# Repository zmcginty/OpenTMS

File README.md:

# Open-Source Transcranial Magnetic Stimulator

An open-source transcranial magnetic stimulator (TMS) project, including coil designs, pulse-generator hardware, and control/charging circuitry.

> **Safety Notice**
> This is **not** a legitimate medical device and is not a substitute for real TMS treatment. This is an experiment I built in my garage, and I cannot verify that it does what it's supposed to (if anyone wants to build an open-source MRI.... let me know...) This device is dangerous, it operates at energy levels more than enough to stop your heart, kill you, blow up and do lots of damage. If you're going to play with high energy pulsed power systems; be careful.

## Table of Contents
- [TMS Coils](#tms-coils)
- [Coil Cooling](#coil-cooling)
- [Coil Materials](#coil-materials)
- [IGBT Switches](#igbt-switches)
- [Gate Drivers](#gate-drivers)
- [Measurement System](#measurement-system)
- [Charging Circuit](#charging-circuit)
- [Pulse-Generator Designs](#pulse-generator-designs)
- [Charge-Control Circuit](#charge-control-circuit)
- [Useful Resources](#useful-resources)
- [TODO](#todo)

---

## TMS Coils

I primarily build two coil geometries — single coils and figure-8 coils. What I've focused on are air-core windings in either single-layer or multi-layer form. The general architecture is adapted from research papers and the limited information published by commercial TMS coil manufacturers. The figure-8 CloudTMS coil (below) was a major influence on my designs in terms of hollow copper conductor carrying coolant.

As I moved to higher pulse rates and energies, active cooling became necessary. My preferred approach, similar to the CloudTMS design, uses hollow copper tubing (sold for HVAC/refrigeration) insulated with PTFE heat-shrink. PTFE works well because it's a good dielectric, stays thin-walled after shrinking, tolerates high temperatures, and holds the coil shape better than thicker heat-shrink alternatives — though it does require fairly high heat to shrink fully.

**Build process:**
- Source 4mm OD / 3mm ID copper tube (5m sections) and 4.5mm, 4:1 PTFE heat-shrink in bulk.
- Feeding heat-shrink onto a long tube run takes patience — compressed air, used to create an air cushion between tube and shrink-wrap, makes this much easier.
- Wind the coil on a custom jig, either single-layer or multi-layer (multi-layer here just means winding randomly around a bobbin rather than stacking discrete single-layer coils).
- Insert something into the copper tube close to the tube's ID (weed-wacker cable works well) during the first few windings to prevent the tube from collapsing, then remove it once winding is complete.
- Hold the coil together with tape ahead of potting.

<p align="center"><em>Example coil before potting</em></p>

Potting the coil in epoxy significantly improves mechanical stability and reduces noise by keeping the windings from moving against each other under pulse forces. Hot glue works as an alternative but produces coils that are noticeably louder in operation — not confidence-inspiring at higher power levels.

<p align="center"><em>Example coil after potting</em></p>

## Coil Cooling

Coils built from hollow copper tube are cooled by pumping coolant through the winding itself.

- **Mineral oil:** Used for a long time — thinner than typical oils but thicker than water. Maintaining ~40°C required roughly 150–200 psi to push enough flow through the coil's small ID. At higher energy levels, I added a water chiller and heat exchanger to pre-cool the oil.
- **Distilled water:** More recently, I've switched to distilled water paired with a diaphragm pump, since the diaphragm provides a degree of electrical isolation between the pump mechanism and the fluid. This is simpler and more effective overall, though there is still a risk of the coolant loop reaching high voltage.

## Coil Materials

| Material | Purpose | Notes |
|---|---|---|
| [Hollow copper tube](https://www.amazon.com/dp/B082FDVNC5) | Water-cooled coil winding | Standard refrigeration-grade tube; cheap and widely available |
| [Fiberglass resin sheet](https://www.amazon.com/dp/B0DYT28W8W) | Application-side coil face | Sturdy, good electrical insulator, and appears permeable to magnetic fields — a disassembled commercial coil used what looked like FR4 fiberglass (PCB-grade) |
| [MAX EPC epoxy potting compound](https://www.amazon.com/dp/B07PMTMKZQ) | Coil potting | Inexpensive, good electrical insulator, decent thermal conductivity. For tube-cooled coils, MAX MCR (lower thermal conductivity) is also an option |

---

## IGBT Switches

My current switch of choice is the **Infineon/Eupec FZ1200R33KF2** — inexpensive and capable of handling substantial power. Prices on eBay range from ~$100–$400, and I've pushed 8kA pulses through a single unit. Adequate snubber capacitance/circuitry is essential to keep the voltage across the device under its 3.3kV rating (I target a safety margin below that).

## Gate Drivers

I've used two Power Integrations gate drivers with this IGBT listed below: but due to limitations and cost, I'm working on designing a custom gate-driver PCB which is still in progress.

- **2SC0535T2G0-33** — Functional, but lacks features like active clamping to protect against turn-off voltage spikes. Requires a custom PCB with gate turn-on/turn-off resistors and capacitors.
- **1SD418F2-FZ1200R33KF2** — Purpose-built for the FZ1200R33KF2; bolts directly onto the device pads. Requires only a 15VDC supply (I use a 1A source). It communicates over two fiber-optic channels (input signal and output/status), which I drive with custom PCBs using AFBR-1624Z HFBR transmitter/receiver modules, controlled by a Teensy 4.1 through a 3.3V→5V level shifter. NOTE: Put fiber-optic receivers (receiving fiber feedback from gate-driver) as close to Teensy/MCU as possible to reduce noise and false fault detection.
- **Custom Gate-Driver (Coming Soon)** — I've noticed that the 1SD418F2 gate drivers I'm using will sometimes detect short-circuits during operation at higher power. This could be legitamite but I'm not exceeding any voltage or current limits as measured by probes. I'm designing a custom gate-driver board since buying gate-drivers new for this IGBT with active-clamping and feedback are over $400, I want to see if I can build them for at most half of that. This will most likely involve having to wind custom isolation-transformers, since I've only found one company who makes isolation transformers rated for ~4-6kV constantly. I've ordered some parts and a 10kV HiPot tester..... more to come later.

---

## Measurement System

### Differential Voltage Measurement
Monitoring Vce (collector-emitter voltage) across each IGBT is critical to staying within its rating — I keep a safety margin and stay below 2.5kV on 3.3kV-rated devices. Since these switches operate on the high side, measurement requires a high-voltage differential probe: I use a **Micsig DP20003** (5600V, 100MHz). A similar, lower-range HV differential probe (1300V) monitors the main capacitor bank voltage.
### Custom HV Diff probe
I'm working on designing a custom HV diff probe since Micsig's new 7kV probe (only other voltage ratings are 700, 1300, 3000) is ~$700, I think it's worth it to try designing a custom probe PCB with isolated dc-dc, voltage divider, and diff opamps. For measuring IGBT voltages, I don't think I need 100MHz bandwidth, so I'm shooting for 50MHz, and hoping to get the price down to less than $100. I'm waiting on boards to show up and will update once I test them! They will probably need to be potted or atleast conformally coated to work in a variety of environments/humidity.

### Current Measurement
A shunt resistor was my first attempt but never produced a trustworthy signal. Two methods have worked well since:

1. **Rogowski coil** — Excellent for high current measurement (AC or DC, no iron core to saturate), but calibrated probes are hard to find secondhand, and a calibrated integrator circuit is needed to get a usable scope signal. I use a calibrated coil from [PowertekUK](https://powertekuk.com) — specifically the [CWTMini](https://powertekuk.com/cwtmini).
2. **Current transformer (CT)** — I use a Tektronix A621 AC current probe (rated to 2kA, available on eBay for $100–$500). In practice, it agrees with the Powertek Rogowski coil up to roughly 8kA despite the rated limit.

---

## Charging Circuit

The charging circuit is a simple, open-loop design: mains power feeds a variable transformer (variac), which drives a microwave oven transformer (MOT) to step up voltage. The stepped-up AC is rectified by a full-bridge rectifier and used to charge the main discharge capacitor bank, which is then discharged through the coil via a high-side switch (latching SCR or non-latching IGBT).

### Microwave Oven Transformers
The current two-switch flyback pulse generator uses two matched MOTs (matched by checking voltage and phase agreement between units — *measurements/resources TODO*). Drawing ~15A at 120V, two matched transformers stay below ~60°C with air cooling alone.

Earlier designs used a single MOT with low-pressure mineral-oil cooling, which worked up to ~14A — but oil cooling systems and pumps added complexity and were prone to leaks.

---

## Pulse-Generator Designs

### Design #1 — SCR-Based Pulse Generator

<p align="center"><em>SCR-switch pulse generator (SCRs are bottom-right. Main capacitor front left. Rectifier behind capacitor. and mineral-oil cooled microwave transformer behid rectifier. </em></p>

The first design I built. It handles very high energy levels well at consistent frequencies/patterns (e.g., the standard 5Hz/10Hz protocols used in early depression-treatment research). Its limitation is pattern flexibility: an SCR/thyristor is a latching switchable diode, so once triggered it fully discharges the capacitor. This steady current decay is gentle on flyback effects but rules out more complex patterns like Theta-Burst (50Hz bursts repeating at 4–5Hz).

### Design #2 — Single-IGBT Pulse Generator

<p align="center"><em>Single IGBT topology (note; two IGBTs in parallel), you can also see gate driver I used before using ones built specifically for the IGBT module</em></p>

Since IGBTs aren't latching, they can be switched on and back off within a short pulse, allowing partial capacitor discharge and enabling patterns like Theta-Burst. The tradeoff is significant flyback voltage when interrupting current through the coil — this destroyed several IGBTs before I addressed it with a robust flyback diode across the coil and snubber capacitors across the IGBT(s) to absorb spikes from parasitic wiring/busbar inductance. HV differential probes are essential here to stay within the switch's voltage rating while tuning.

This design uses a flyback diode across the coil, producing a sharp current rise but a slow fall (as flyback energy dissipates through coil/wire resistance and the diode). It worked well and was relatively simple compared to the two-switch flyback design, but since flyback energy isn't recycled, it's ultimately limited by the 120V/15A charging circuit.

### Design #3 — Two-Switch Flyback IGBT Pulse Generator

<p align="center"><em>Two-Switch flyback topology being built. You can see the diodes hanging off to the sides. And gate drives are now on the left, bolted to IGBT modules behind bus-bars.</em></p>

This design recycles more pulse energy than the single-IGBT version and produces both a sharp rising *and* falling current edge, increasing di/dt for a stronger but shorter magnetic field pulse. It noticeably reduced charging-circuit current draw and appears more effective at stimulating muscle/nerve tissue than the single-switch design, even at higher peak current — likely because faster field transitions induce greater current in tissue.
+ For this design it's important to thermally bond both IGBT/switch modules so that they're the same temperature and have the same switching characteristics. For this I bolt them each to opposite sides of an aluminum plate which I attach water-cooling blocks to.
I've been realizing the importance of keeping switching loops tight, and have shortened cabling from capacitor to IGBTs, and shortening cables from IGBTs to diodes.

<p align="center"><em>Photo of the system, from left-to-right; charge-control board, multimeter, main pulse-IGBTs (with many red snubber caps), charge-control IGBT (with single red snubber in front), charge-circuit-rectifier, and main pulse capacitor bank in back </em></p>

### Design #4 — H-Bridge IGBT Pulse Generator (Not Yet Built)
Should double coil pulse current relative to the two-switch flyback topology by enabling current reversal. The complexity of positioning four large IGBT switches and the associated snubbers and diodes close to eachother, with cooling is going to be difficult without adding parasitic inductance that would offset the gains.

---
## Phase-Controlled Rectifier

<p align="center"><em>Jankily built phase-control rectum-fryer, with o-smelliscope for proof</em></p>

I've built a phase control rectum-fryer, it works! Gotta increase the chooch-factor of the gate drivers primary drive-transistors a bit because the giant SCRs I'm using are thirsty (I think this is causing the ripple in the output waveform). Still TODO here is add another DAC for the teensy to control the phase-angle the controlled rectumfryer fires at (how much of the wave it turns to DC), and add all the PID loops and stuff here. Also, just ignore the fact that the output waveform is upside-downwards in the photo. I'll flip it I promise.

Update; I'm seeing weird behavior when adding a microwave trasformer to step up voltage, the AC waveform gets heavily distorted when I begin triggering the SCRs, and they don't seem to be fully triggering..... It works fine at the same voltage coming straight from the variable transformer, but doesn't work going through the microwave step-up transformer.

## Charge-Control Circuit

<p align="center"><em>Re-Packaged Charge-Control and Pulse-Firing Controllers, and put them in a shielded box since having a small EMP right next to it APARENTLY causes EMI issues.</em></p>

Charge controller and Pulse firing control circuits are working much better now that they're in a shielded box. No more noise causing false gate-driver faults. Which allowed me to actually see that I am sometimes getting a real fault from the gate-drivers causing them to shut off for a few seconds. I think this is not actually an over-current condition and will try to prove it. But I'm working on designing (with help from claude) a new gate-driver board for these which will report errors and let the main controller decide what to do about it.
Charge-Controller is no longer using an external ADS1115 ADC, but rather using both internal ADCs on the teensy which are noisier but much faster. Utilizing voltage dividers to bring signals down from 5v to 3.3v to keep the magic smoke in.

<p align="center"><em>Screenshot of a python script which displays a realtime graph and telemetry from the serial output of the teensy charge-control. Also added the ability to adjust the charge-setpoint in the python window. You can see the pulse trains as the capacitor discharges. I've added a calibration-tab here for calibrating the ADCs. I think this will change once I integrate the phase-control rectifier.</em></p>

Above is a screenshot of a python script which listens to voltage values sent over serial from the teensy charge controller and will display a live graph of the capacitor voltage, which is really useful for debugging as it's basically an autoscaling slow oscilliscope. The graph only shows the fast ADC's (ADS8699) calibrated capacitor voltage. It also displays other, slow-speed telemetry as numbers such as the slow ADC's calibrated capacitor voltage, slow ADC's measurement of DAC's output in both raw voltage, and the scaled/calibrated set-voltage it corresponds to (ie. I set the DAC to output a voltage which corresponds to 200V from the Micsig, I can verify that the ADC's measurement reads close enough, like 199.2V) I also added control to adjust the voltage setpoint from this python window which is useful for testing system starting from low voltage to be safe. I think there may be something with the comparator which is causing the cutoff to be slightly below the setpoint; in the screenshot you can see it cutting at ~95V instead of 100V. More calibrations....

---
## Coil Field Simulation
While I've built coils similar to what other systems use, I have difficulty understanding how fields from multiple coils interract/interfere to create focused peaks. I've asked Claude to build some tools to help visualise magnetic field strength in a 3-d map of various types of coils here [Coil_Field_Simulator_Scripts](Coil_Field_Simulator_Scripts/).
 The simulations show for instance what happens to the field when you reverse current of one of the two figure-8 windings, or have the two coils overlap. I'm hoping that I can gather data with the Coil-Field Measurement System mentioned below, to confirm what these simulations show.
I know that TMS companies construct special coils for studies called "sham-coils" which are meant to make the same sound, but the windings are wired such that the two halves of the figure-8 cancel out. These coils are used for TMS efficacy studies to give someone placebo treatment. 

## Coil Field Mapping System
I've begun the coil-measurement system! at the moment I only have the data-acquisition side built and working which is in [Coil-Field_Measurement_DAQ](Coil-Field_Measurement_DAQ/), and will have to integrate this with a 3-axis machine to move a probe around the coil to take measurements. 
As much as I wanted to use a high-speed ADC and teensy to measure pulses, it would have been alot of work to read and buffer 1M samples/s.... So I decided to use a faster USB oscilliscope instead; [DreamSourceLab DSCope](https://www.dreamsourcelab.com/product/dscope-series/) and had Claude write some python scripts which access it via the sigrok library, and visualize the results of the measurements it takes. Note; the scope I have which this code is built to interface with is a DSCope B20. 
- CH0 of the scope is measuring custom magnetic probe (a small coil of magnet-wire connected to RG316 shielded cable) 
- CH1 of the scope measures a rogowski current probe measuring the current through the coil, this is so the magentic fieldn strength can be scaled by the measured current to account for any difference in pulse strength.

## Safety Resources
- [TMS Safety with respect to seizures](https://pmc.ncbi.nlm.nih.gov/articles/PMC7732158/pdf/ndt-16-2989.pdf)
- [General article discussion factors which can decrease seizure-threshold (make it more likely you'll have a seizure)](https://www.wmchealth.org/living-well/7-everyday-factors-that-can-increase-seizure-risk)
- [Concise overview from clinic of seizure risk factors](https://www.midcitytms.com/transcranial-magnetic-stimulation-safety-with-respect-to-seizure-ndt/)

## Useful Resources

- [Online calculator used for Beam-Protocol/10-20 system to calculate position of DLPFC](https://clinicalresearcher.org/F3/calculate.php)
- [Same online calculator, where you enter your measurements](https://clinicalresearcher.org/F3/)
- [Clinical Researcher Software Tools (where I got the two links above) Contains other tools that could be useful for motor-threshold stuff](https://clinicalresearcher.org/software.htm)

## Useful Videos
- [Coil placement and the 10-20 system/beam protocol (video)](https://youtu.be/CKCvAkgdJuY?si=6TRw3_EgRK5eAh5G)
- [Same video as above with added instructions to enter measurements into clinicalresearcher calculator (link above)](https://youtu.be/akp4V5PFb6A?si=kvKB5cpgHWPCvdm8)
- [Good introductory explanation of general TMS](https://www.youtube.com/watch?v=NQHVfF_5rtc)
- [Funny video of the TMS researcher interrupting his speach with TMS](https://www.youtube.com/watch?v=85QKdt8boMA)
- [Researcher showing TMS stimulating muscles directly and muscles through the motor-cortex](https://www.youtube.com/watch?v=JA0q4fVqrFQ)
- [Good Long-Form explanation of someone who runs a TMS clinic showing how they get a patient setup, and perform treatment](https://www.youtube.com/watch?v=WxCunEG2oi0)

## TODO
1. **UPDATE THE SCHEMATICS**
2. **Refine charge-control switch** The charge controller is working well now. But I'm using a rediculously big IGBT to switch just a few tens of amps. Need to find a smaller IGBT/switch which can withstand ~2-3kV to be on the safe-side.
3. **Finish Integrating phase-control rectifier** I've built a phase control rectum-fryer, it works. Gotta increase the chooch-factor of the gate drivers primary drive-transistors a bit because the giant SCRs I'm using are thirsty. Still TODO here is add another DAC for the teensy to control the phase-angle the controlled rectumfryer fires at (how much of the wave it turns to DC), and add all the PID loops and stuff here. 
4. **Process gate-driver fault feedback** Reading status/feedback from gate-drivers is working now and has latching/blinking LEDs/indicators to indicate warnings and faults. There is functionality to turn off a safety relay, disconnecting power from a subsystem or whole system which I'll get wired up later.
5. **Extend functionality to Pulse-Driver Teensy** I'd like to add the ability to run different patterns/protocols, maybe add input (with damn good shielding) so user can press a button to fire a single pulse. And add the ability to choose different pulse-patters, like various continuous or intermittent rTMS(repetitive) frequencies. Also various TBS-based protocols (Thea-Burst Stim); continuous (cTBS) and intermittent (iTBS) with adjustments for various parameters such as train-frequency, inter-train delay and such.
6. **Finally build a tool to map the magnetic field strength & shape of a coil.** My idea is basically put a precise analog hall-effect sensor on some 3d gantry machine like a 3d printer, and have it scan over many 3d points around the coil and create a 3d heat-map of magnetic field strength. Anyone know how to use 3d-printers? and know how to make them scan some end-effector to create a map like this???? I'd love some help!
7. **Better Shielding / Shielded Enclosure** This is basically a small EMP... so I find myself having to filter out interference on EVERYTHING at exactly the time the IGBT turns off (the turn-off spike). What if I just put everything in a shielded/grounded metal box??? Surely it wouldn't be that easy right??
8. **Create Bill-Of-Materials for each design** Create BOMs for what parts I've used in the various designs of TMS systems. Most coil materials are the same. But it would be useful to have BOMs for the SCR-based and IGBT-based pulse-generator designs.
9. **Maybe implement Micsig's command and control protocol over USB/serial** Micsig's command and control interface can configure the voltage range and bandwidth of the probe, and can read the probes serial number. Reading the serial number would allow the control software to load a specific calibration for a specific serial number of probe to ensure accuracy. Could also have a fallback/safe mode the system could operate in when connected to uncalibrated probes.

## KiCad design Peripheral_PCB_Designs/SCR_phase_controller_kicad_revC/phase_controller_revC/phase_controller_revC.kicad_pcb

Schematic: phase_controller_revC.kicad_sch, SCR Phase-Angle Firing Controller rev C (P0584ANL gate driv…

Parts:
C1, C23: 100u 100V; CP_Radial_D10.0mm_P5.00mm
C2, C24: 100n 100V; C_0805_2012Metric
C3, C5: 10u 25V; C_1206_3216Metric
C4, C6, C9, C11, C12, C14, C16, C19, C20, C22, C32: 100n; C_0805_2012Metric
C7, C8, C18: 2n2 C0G; C_0805_2012Metric
C10: 470p; C_0805_2012Metric
C13: 100n film (MKS2); C_Rect_L7.2mm_W3.5mm_P5.00mm_FKS2_FKP2_MKS2_MKP2
C15, C17, C28, C29, C30, C31: 10n; C_0805_2012Metric
C25: 10u 50V; C_1206_3216Metric
C26: 100u 63V; CP_Radial_D8.0mm_P3.50mm
C27, C33: 2u2 100V X7R; C_1210_3225Metric
D1, D17: MB2S; TO-269AA
D5: GRN PWR; LED_D3.0mm
D7, D8, D9, D10: BAT54S; SOT-23
D11, D27, D33, D39, D45: 1N4148W; D_SOD-123
D12: YEL FIRING; LED_D3.0mm
D13, D15: ES1D; D_SMA
D14, D16: BZT52C15; D_SOD-123
D22, D28, D34, D40: SMAJ15CA; D_SMA
D23, D29, D35, D41: CDBHM140-HF; TO-269AA
F1: 100mA T (5x20); Fuseholder_Cylinder-5x20mm_Schurter_0031_8201_Horizontal_Op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
H1: PE bond M3; MountingHole_3.2mm_M3_Pad_Via
H2, H3, H4: M3; MountingHole_3.2mm_M3
J1: MAINS L/N/PE (115V); TerminalBlock_Phoenix_MKDS-1,5-3-5.08_1x03_P5.08mm_Horizont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
J3: CONTROL (Teensy); PinHeader_1x06_P2.54mm_Vertical
J6: EXT GDT SUPPLY <=48V; TerminalBlock_Phoenix_MKDS-1,5-2-5.08_1x02_P5.08mm_Horizont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
J7: GATE A1 (G,K); TerminalBlock_Phoenix_MKDS-1,5-2-5.08_1x02_P5.08mm_Horizont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
J8: GATE A2 (G,K); TerminalBlock_Phoenix_MKDS-1,5-2-5.08_1x02_P5.08mm_Horizont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
J9: GATE B1 (G,K); TerminalBlock_Phoenix_MKDS-1,5-2-5.08_1x02_P5.08mm_Horizont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
J10: GATE B2 (G,K); TerminalBlock_Phoenix_MKDS-1,5-2-5.08_1x02_P5.08mm_Horizont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
JP4: 3V3 IN GAIN x1.51; PinHeader_1x02_P2.54mm_Vertical
JP5: CUT TO INJECT; SolderJumper-2_P1.3mm_Bridged_RoundedPad1.0x1.5mm
Q3: 2N7002; SOT-23
Q4: MMBT3906; SOT-23
Q5, Q6: FQD13N10L; TO-252-2
R1, R15: 4k7; R_0805_2012Metric
R2, R5: 150k; R_1206_3216Metric
R3, R4, R6, R7: 20k 1%; R_0805_2012Metric
R8: 9k53 1%; R_0805_2012Metric
R9: 10k2 1%; R_0805_2012Metric
R10, R12: 2M2; R_0805_2012Metric
R11, R13, R14, R18, R22, R28, R37, R40: 10k; R_0805_2012Metric
R16, R23: 47k; R_0805_2012Metric
R17: 27k; R_0805_2012Metric
R21, R53, R55, R57, R59: 100; R_0805_2012Metric
R24: 22k; R_0805_2012Metric
R25, R35, R42, R44: 1k; R_0805_2012Metric
R26: 100k; R_0805_2012Metric
R27: 5k1; R_0805_2012Metric
R29, R30, R31, R32: 10k 0.1%; R_0805_2012Metric
R33: 3k3; R_0805_2012Metric
R34: 39k; R_0805_2012Metric
R36, R39: 22; R_0805_2012Metric
R38, R41, R50, R51: 120R 1W; R_2512_6332Metric
R43, R45: 2k; R_0805_2012Metric
R46, R48: 240 1%; R_0805_2012Metric
R47: 2k05 1%; R_0805_2012Metric
R49: 4k32 1%; R_0805_2012Metric
R52, R54, R56, R58: 2R2; R_1206_3216Metric
RV1: S10K150; RV_Disc_D12mm_W4.2mm_P7.5mm
RV2: 10k RAMP CAL; Potentiometer_Bourns_3296W_Vertical
RV3: 10k MAX POWER; Potentiometer_Bourns_3296W_Vertical
T1: BV301D24028; Zettler_EI30_2xSec
T2, T3: P0584ANL; Pulse_P0584ANL
TP1: RAMP; TestPoint_Loop_D2.50mm_Drill1.0mm
TP2: FIRE_THRESHOLD; TestPoint_Loop_D2.50mm_Drill1.0mm
TP3: HALF_L_POS; TestPoint_Loop_D2.50mm_Drill1.0mm
TP4: HALF_L_NEG; TestPoint_Loop_D2.50mm_Drill1.0mm
TP5: ZERO_CROSS; TestPoint_Loop_D2.50mm_Drill1.0mm
TP6: FIRE_AND_ENABLE; TestPoint_Loop_D2.50mm_Drill1.0mm
TP7: PULSE_TRAIN; TestPoint_Loop_D2.50mm_Drill1.0mm
TP8, TP10: GND; TestPoint_Loop_D2.50mm_Drill1.0mm
TP9: SYNC_L_SENSE; TestPoint_Loop_D2.50mm_Drill1.0mm
TP11: VGDT; TestPoint_Loop_D2.50mm_Drill1.0mm
U1, U7: LM317HVT; TO-220-3_Vertical
U2: L7805; TO-220-3_Vertical
U3: LM339; SOIC-14_3.9x8.7mm_P1.27mm
U4: MCP6002; SOIC-8_3.9x4.9mm_P1.27mm
U5: TLC555; SOIC-8_3.9x4.9mm_P1.27mm
U6: 74HC08; SOIC-14_3.9x8.7mm_P1.27mm
U8: 74AHC1G02; SOT-23-5

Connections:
+5V: C5.1, C6.1, C19.1, C20.1, C22.1, C32.1, D7.2 (K), D8.2 (K), D9.2 (K), D10.2 (K), R3.1, R6.1, R8.1, R11.1, R13.1, R14.1, R17.1, R29.1, R33.1, U2.3 (OUT), U4.8 (V+), U5.8 (VCC), U6.14 (VCC), U8.5 (VCC)
+12V: C3.1, C4.1, C12.1, C14.1, R1.1, R22.1, R24.1, R46.1, U1.2 (VO), U2.1 (IN), U3.3 (V+)
+24V_REG: C25.1, JP5.1 (A), R48.1, U7.2 (VO)
BUF_FEEDBACK: R27.2, R28.1, U4.2 (-)
CTRL_BUFFERED: R27.1, R31.1, U4.1
CTRL_CLAMPED: C15.1, D10.3 (COM), R25.2, R26.1, RV3.1
CTRL_IN: J3.2, R25.1
CTRL_SCALED: RV3.2, U4.3 (+)
DRIVE_A: R36.1, U6.3
DRIVE_B: R39.1, U6.6
ENABLE_DIV: D9.3 (COM), R15.2, R16.1, U3.9 (+)
ENABLE_IN: J3.3, R15.1
ENABLE_REF_1V35: C11.1, R17.2, R18.1, U3.8 (-)
FIRE_AND_ENABLE: C10.1, R14.2, TP6.1, U3.13, U3.14, U5.4 (R), U6.9, U6.10
FIRE_THRESHOLD: R32.2, TP2.1, U3.10 (-), U4.7
FIRING_5V: R35.1, R44.1, U6.8
FIRING_OUT_3V3: J3.5, R44.2, R45.1
GAIN_JUMPER: JP4.1 (A), R28.2
GDT_A_CLAMP: D13.1 (K), D14.1 (K)
GDT_A_DRAIN: D13.2 (A), Q5.2 (D), T2.10 (DRV-)
GDT_A_SUPPLY: D14.2 (A), R38.2, R50.2, T2.1 (DRV+)
GDT_B_CLAMP: D15.1 (K), D16.1 (K)
GDT_B_DRAIN: D15.2 (A), Q6.2 (D), T3.10 (DRV-)
GDT_B_SUPPLY: D16.2 (A), R41.2, R51.2, T3.1 (DRV+)
GND: C1.2, C2.2, C3.2, C4.2, C5.2, C6.2, C7.2, C8.2, C9.2, C10.2, C11.2, C12.2, C13.2, C15.2, C16.2, C17.2, C18.2, C19.2, C20.2, C22.2, C23.2, C24.2, C25.2, C26.2, C27.2, C32.2, C33.2, D1.4 (-), D5.1 (K), D7.1 (A), D8.1 (A), D9.1 (A), D10.1 (A), D12.1 (K), D17.4 (-), J3.1, J3.6, J6.2, JP4.2 (B), Q3.2 (S), Q5.3 (S), Q6.3 (S), R4.2, R7.2, R9.2, R16.2, R18.2, R23.2, R26.2, R30.2, R37.2, R40.2, R43.2, R45.2, R47.2, R49.2, RV3.3, TP8.1, TP10.1, U2.2 (GND), U3.12 (V-), U4.4 (V-), U5.1 (GND), U6.7 (GND), U8.3 (GND)
HALF_L_NEG: R12.1, R13.2, TP4.1, U3.1, U6.5, U8.2
HALF_L_POS: R10.1, R11.2, TP3.1, U3.2, U6.2, U6.12, U6.13, U8.1
INV_INPUT: R31.2, R32.1, U4.6 (-)
LED_FIRING: D12.2 (A), R35.2
LED_POWER: D5.2 (A), R1.2
MAINS_L: F1.1, J1.1
MAINS_L_FUSED: F1.2, RV1.1, T1.1 (PRI)
MAINS_N: J1.2, RV1.2, T1.5 (PRI)
OUT_A1_CATHODE: C28.2, D23.4 (-), D27.2 (A), J7.2, R53.2
OUT_A1_GATE: C28.1, D27.1 (K), J7.1, R52.2, R53.1
OUT_A1_RECTIFIED: D23.3 (+), R52.1
OUT_A1_WINDING: D22.2 (A2), D23.2, T2.4 (G1-)
OUT_A1_WINDING_DOT: D22.1 (A1), D23.1, T2.3 (G1+)
OUT_A2_CATHODE: C29.2, D29.4 (-), D33.2 (A), J8.2, R55.2
OUT_A2_GATE: C29.1, D33.1 (K), J8.1, R54.2, R55.1
OUT_A2_RECTIFIED: D29.3 (+), R54.1
OUT_A2_WINDING: D28.2 (A2), D29.2, T2.7 (G2-)
OUT_A2_WINDING_DOT: D28.1 (A1), D29.1, T2.8 (G2+)
OUT_B1_CATHODE: C30.2, D35.4 (-), D39.2 (A), J9.2, R57.2
OUT_B1_GATE: C30.1, D39.1 (K), J9.1, R56.2, R57.1
OUT_B1_RECTIFIED: D35.3 (+), R56.1
OUT_B1_WINDING: D34.2 (A2), D35.2, T3.4 (G1-)
OUT_B1_WINDING_DOT: D34.1 (A1), D35.1, T3.3 (G1+)
OUT_B2_CATHODE: C31.2, D41.4 (-), D45.2 (A), J10.2, R59.2
OUT_B2_GATE: C31.1, D45.1 (K), J10.1, R58.2, R59.1
OUT_B2_RECTIFIED: D41.3 (+), R58.1
OUT_B2_WINDING: D40.2 (A2), D41.2, T3.7 (G2-)
OUT_B2_WINDING_DOT: D40.1 (A1), D41.1, T3.8 (G2+)
PE: H1.1, J1.3
PULSE_TRAIN: TP7.1, U5.3 (Q), U6.1, U6.4
Q5_GATE: Q5.1 (G), R36.2, R37.1
Q6_GATE: Q6.1 (G), R39.2, R40.1
RAMP: C13.1, Q4.3 (C), R21.2, TP1.1, U3.11 (+)
RAMP_RESET: Q3.3 (D), R21.1
RAMP_SRC_BASE: C14.2, Q4.1 (B), R22.2, R23.1
RAMP_SRC_EMITTER: Q4.2 (E), RV2.2, RV2.3
RAMP_SRC_TRIM: R24.2, RV2.1
REF_2V5: C16.1, R29.2, R30.1, U4.5 (+)
REG12_ADJ: R46.2, R47.1, U1.1 (ADJ)
REG24_ADJ: R48.2, R49.1, U7.1 (ADJ)
SYNC_5V: R42.1, U6.11
SYNC_L_SENSE: C7.1, D7.3 (COM), R2.2, R3.2, R4.1, R10.2, TP9.1, U3.5 (+)
SYNC_N_SENSE: C8.1, D8.3 (COM), R5.2, R6.2, R7.1, R12.2, U3.7 (+)
SYNC_OUT_3V3: J3.4, R42.2, R43.1
SYNC_THRESHOLD: C9.1, R8.2, R9.1, U3.4 (-), U3.6 (-)
TIMER_CAP: C18.1, D11.1 (K), R34.2, U5.2 (TR), U5.6 (THR)
TIMER_CV: C17.1, U5.5 (CV)
TIMER_DISCH: D11.2 (A), R33.2, R34.1, U5.7 (DIS)
VGDT: C26.1, C27.1, C33.1, J6.1, JP5.2 (B), R38.1, R41.1, R50.1, R51.1, TP11.1
VRAW_GDT: C23.1, C24.1, D17.3 (+), U7.3 (VI)
VRAW_LOGIC: C1.1, C2.1, D1.3 (+), U1.3 (VI)
XFMR_GDT: D17.2, T1.9 (SB-)
XFMR_GDT_DOT: D17.1, T1.10 (SB+)
XFMR_LOGIC: D1.2, R5.1, T1.6 (SA-)
XFMR_LOGIC_DOT: D1.1, R2.1, T1.7 (SA+)
ZERO_CROSS: Q3.1 (G), TP5.1, U8.4

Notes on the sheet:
~7us ON / ~59us OFF (first pulse ~10us) so the P0584ANL flux stays below its 2100 G limit (unipolar: B = 33 x ET).
LINEAR RAMP (constant-current PNP, reset every zero crossing). RV2: set ramp peak = 4.8V on TP1 RAMP
ISOLATED GATE OUTPUTS, CH A (fires when L positive). Schottky bridge makes each output polarity-proof. Each output floats at its SCR cathode
GDT DRIVER B: VGDT -> R41||R51 -> P0584ANL T3 -> Q6. C33 = local 2u2 at Q6 source.
CONTROL HEADER (3.3V-safe outputs), INDICATORS, TEST POINTS, MOUNTING
A1/A2 are driven together (same transformer) - use one per SCR, e.g. paralleled SCRs or the 2 SCRs of a half-controlled bridge.
the on-board VGDT supports ~0.4A pulses at ~10% duty. For harder firing inject an external supply (cut JP5 first!).
GDT DRIVER A: VGDT -> R38||R50 (sets pulse current) -> P0584ANL T2 -> Q5. D13+D14 reset the core (~16V). C27 = local 2u2 at Q5 source.
CONTROL INPUT 0-5V (JP4 fitted: 0-3.3V) -> FIRE_THRESHOLD = 5V - Vin. 0V = OFF (180 deg), 5V = full ON
D13+D14 (D15+D16, ES1D + BZT52C15) reset the core at ~16V between pulses. C27/C33 close the pulse loop at each MOSFET source. Q5/Q6 are 100V parts: VGDT + 16V must stay < 80V.
CALIBRATION: RV2 -> ramp peak 4.8V on TP1 (RAMP). TP3 (HALF_L_POS) is high while L is positive.
SYNC (winding A, in phase with L) -> HALF_L_POS / HALF_L_NEG + ZERO_CROSS window ZERO_CROSS = NOR(HALF_L_POS, HALF_L_NEG) in U8.
GATE-DRIVE RAIL: winding B -> LM317HV 23.8V -> JP5 (bridged) -> VGDT. To inject: CUT JP5, feed J6 (<=48V, scale R38/R41)
OUTPUTS: each gate winding -> TVS -> CDBHM140 Schottky bridge (polarity-proof) -> 2R2 -> G, with 100R / 10nF / 1N4148W at G-K.
Timing chain (sync, ramp, FIRE_THRESHOLD = 5V - Vin, FIRE_AND_ENABLE, gated 555, steering) is unchanged from rev A, except the pulse train is shorter:
FIRE_AND_ENABLE = (RAMP > FIRE_THRESHOLD) AND (ENABLE_IN > 1.35V). ENABLE_IN low/floating = NO GATE PULSES
ISOLATED GATE OUTPUTS, CH B (fires when L negative)
See docs/THEORY_OF_OPERATION.md for a block-by-block walkthrough and a net-name glossary.
Pulse current ~ (VGDT - 4V) / (R38||R50). 24V with 2x120R -> ~0.35A (fits the 2.8VA budget); 48V injected -> 2x220R (~0.4A) ... 2x120R (~0.75A). Keep each 2512 < 1W.
GATED PULSE TRAIN (~15kHz: ~7us ON, first pulse ~10us; keeps P0584ANL < 2100 G) + STEERING DRIVE_A = PULSE_TRAIN & HALF_L_POS, DRIVE_B = PULSE_TRAIN & HALF_L_NEG
MAINS INPUT 115V + ZETTLER BV301D24028 (2x24V 58mA, 2x42V no-load). Winding A: logic + sync, winding B: gate-drive rail
POWER: Zettler secondaries are 24V at 58mA but ~42V unloaded, so both rails use LM317HV (60V rated). 2.8VA total budget:
THEORY OF OPERATION (rev C)
LOGIC SUPPLY: winding A -> VRAW_LOGIC (33..58V) -> LM317HV 12V -> 7805 5V
GATE DRIVE: Q5/Q6 switch VGDT through R38||R50 (R41||R51) into the P0584ANL drive winding (current drive).

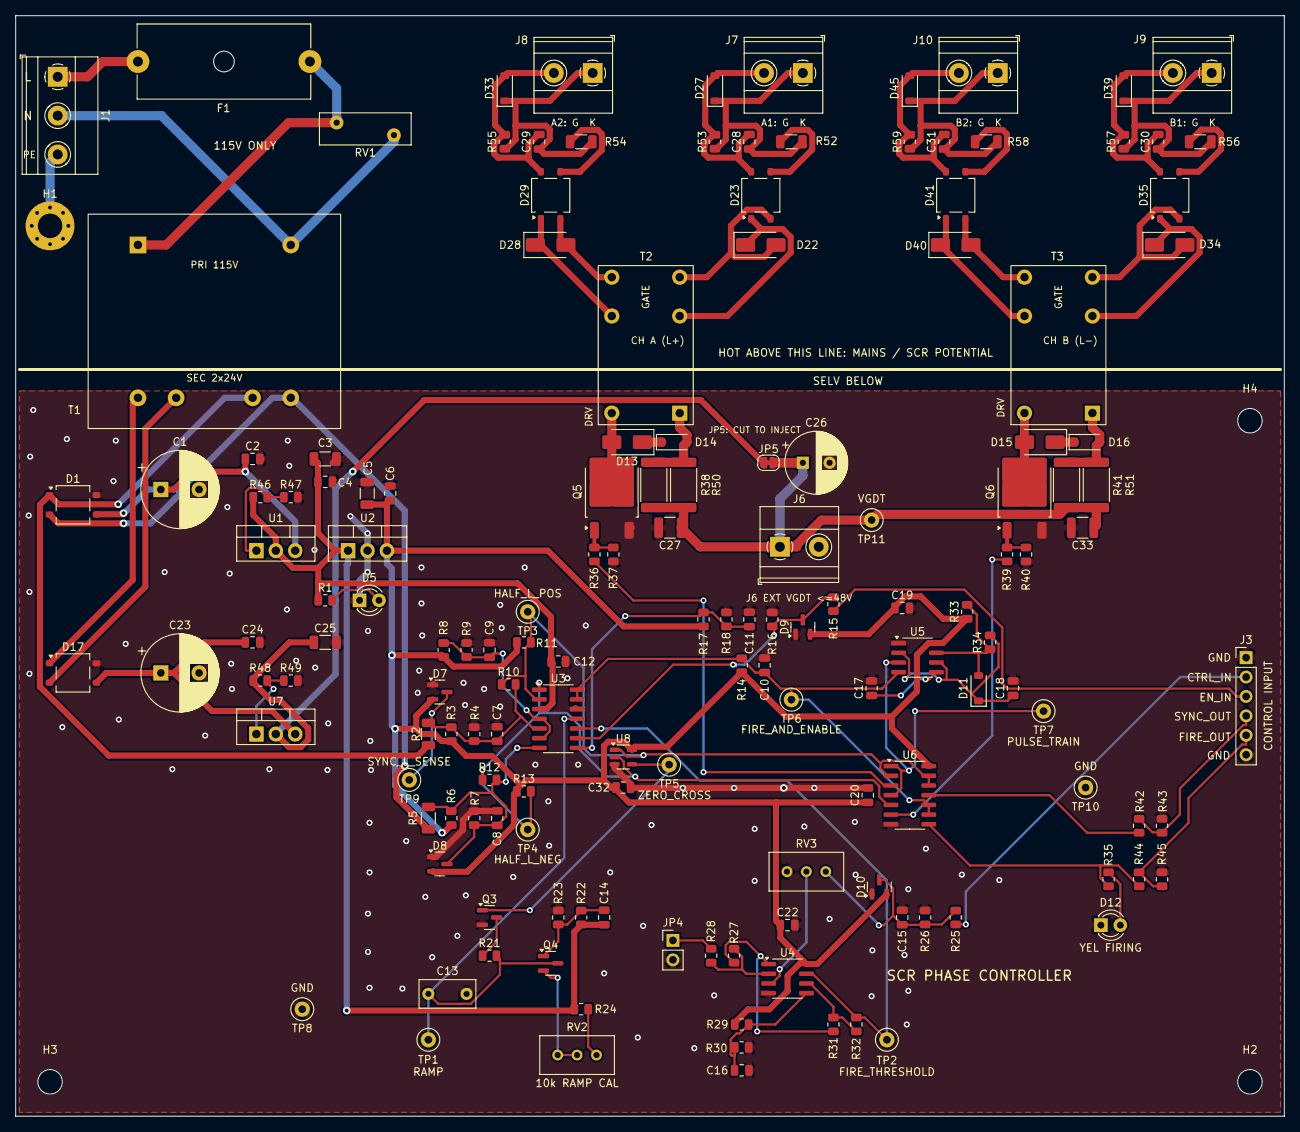
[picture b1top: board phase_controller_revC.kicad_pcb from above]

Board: 2 copper layers, 166.0 x 144.0 mm, 157 parts (0 on the bottom side), 81 nets.

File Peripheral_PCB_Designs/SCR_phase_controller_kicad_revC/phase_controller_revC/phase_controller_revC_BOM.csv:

Qty,References,Value,Footprint,Suggested part / notes
2,C1 C23,100u 100V,CP_Radial_D10.0mm_P5.00mm,"100uF 100V radial 10mm, 5mm pitch"
2,C2 C24,100n 100V,C_0805_2012Metric,
2,C3 C5,10u 25V,C_1206_3216Metric,
11,C4 C6 C9 C11 C12 C14 C16 C19 C20 C22 C32,100n,C_0805_2012Metric,
3,C7 C8 C18,2n2 C0G,C_0805_2012Metric,
1,C10,470p,C_0805_2012Metric,
1,C13,100n film (MKS2),C_Rect_L7.2mm_W3.5mm_P5.00mm_FKS2_FKP2_MKS2_MKP2,"WIMA MKS2 100nF 63V (5mm) or any PET/PP film, 5mm pitch"
6,C15 C17 C28 C29 C30 C31,10n,C_0805_2012Metric,
1,C25,10u 50V,C_1206_3216Metric,
1,C26,100u 63V,CP_Radial_D8.0mm_P3.50mm,"100uF 63V radial 8mm, 3.5mm pitch"
2,C27 C33,2u2 100V X7R,C_1210_3225Metric,2.2uF 100V X7R 1210 (e.g. Murata GRM32ER72A225KA35L)
2,D1 D17,MB2S,TO-269AA,"Vishay MB2S (200V 0.5A bridge, TO-269AA/MBS)"
1,D5,GRN PWR,LED_D3.0mm,
4,D7 D8 D9 D10,BAT54S,SOT-23,
5,D11 D27 D33 D39 D45,1N4148W,D_SOD-123,
1,D12,YEL FIRING,LED_D3.0mm,
2,D13 D15,ES1D,D_SMA,"Vishay/Diodes ES1D (200V 1A fast, SMA)"
2,D14 D16,BZT52C15,D_SOD-123,"BZT52C15 (15V 500mW, SOD-123)"
4,D22 D28 D34 D40,SMAJ15CA,D_SMA,SMAJ15CA (bidirectional)
4,D23 D29 D35 D41,CDBHM140-HF,TO-269AA,"Comchip CDBHM140-HF or CDBHM140L-HF (40V 1A Schottky bridge, MBS/TO-269AA) - check pinout: 1,2 = AC, 3 = +, 4 = -"
1,F1,100mA T (5x20),Fuseholder_Cylinder-5x20mm_Schurter_0031_8201_Horizontal_Open,Schurter 0031.8201 holder + 0853.0551 cover; fuse 5x20 100mA T
1,H1,PE bond M3,MountingHole_3.2mm_M3_Pad_Via,
3,H2 H3 H4,M3,MountingHole_3.2mm_M3,
1,J1,MAINS L/N/PE (115V),"TerminalBlock_Phoenix_MKDS-1,5-3-5.08_1x03_P5.08mm_Horizontal","Phoenix Contact MKDS 1,5/ 3-5,08 (1715734)"
1,J3,CONTROL (Teensy),PinHeader_1x06_P2.54mm_Vertical,1x6 2.54mm pin header
1,J6,EXT GDT SUPPLY <=48V,"TerminalBlock_Phoenix_MKDS-1,5-2-5.08_1x02_P5.08mm_Horizontal","Phoenix Contact MKDS 1,5/ 2-5,08 (1715721)"
1,J7,"GATE A1 (G,K)","TerminalBlock_Phoenix_MKDS-1,5-2-5.08_1x02_P5.08mm_Horizontal","Phoenix Contact MKDS 1,5/ 2-5,08 (1715721)"
1,J8,"GATE A2 (G,K)","TerminalBlock_Phoenix_MKDS-1,5-2-5.08_1x02_P5.08mm_Horizontal","Phoenix Contact MKDS 1,5/ 2-5,08 (1715721)"
1,J9,"GATE B1 (G,K)","TerminalBlock_Phoenix_MKDS-1,5-2-5.08_1x02_P5.08mm_Horizontal","Phoenix Contact MKDS 1,5/ 2-5,08 (1715721)"
1,J10,"GATE B2 (G,K)","TerminalBlock_Phoenix_MKDS-1,5-2-5.08_1x02_P5.08mm_Horizontal","Phoenix Contact MKDS 1,5/ 2-5,08 (1715721)"
1,JP4,3V3 IN GAIN x1.51,PinHeader_1x02_P2.54mm_Vertical,1x2 2.54mm header + shunt
1,JP5,CUT TO INJECT,SolderJumper-2_P1.3mm_Bridged_RoundedPad1.0x1.5mm,"solder jumper, bridged - cut trace to inject external VGDT"
1,Q3,2N7002,SOT-23,2N7002
1,Q4,MMBT3906,SOT-23,MMBT3906
2,Q5 Q6,FQD13N10L,TO-252-2,onsemi FQD13N10LTM (100V logic-level)
2,R1 R15,4k7,R_0805_2012Metric,
2,R2 R5,150k,R_1206_3216Metric,
4,R3 R4 R6 R7,20k 1%,R_0805_2012Metric,
1,R8,9k53 1%,R_0805_2012Metric,
1,R9,10k2 1%,R_0805_2012Metric,
2,R10 R12,2M2,R_0805_2012Metric,
8,R11 R13 R14 R18 R22 R28 R37 R40,10k,R_0805_2012Metric,
2,R16 R23,47k,R_0805_2012Metric,
1,R17,27k,R_0805_2012Metric,
5,R21 R53 R55 R57 R59,100,R_0805_2012Metric,
1,R24,22k,R_0805_2012Metric,
4,R25 R35 R42 R44,1k,R_0805_2012Metric,
1,R26,100k,R_0805_2012Metric,
1,R27,5k1,R_0805_2012Metric,
4,R29 R30 R31 R32,10k 0.1%,R_0805_2012Metric,
1,R33,3k3,R_0805_2012Metric,
1,R34,39k,R_0805_2012Metric,
2,R36 R39,22,R_0805_2012Metric,
1,R38,120R 1W,R_2512_6332Metric,120R 1W 2512 (2x per channel; 48V inject: 2x220R)
3,R41 R50 R51,120R 1W,R_2512_6332Metric,120R 1W 2512
2,R43 R45,2k,R_0805_2012Metric,
2,R46 R48,240 1%,R_0805_2012Metric,
1,R47,2k05 1%,R_0805_2012Metric,
1,R49,4k32 1%,R_0805_2012Metric,
4,R52 R54 R56 R58,2R2,R_1206_3216Metric,
1,RV1,S10K150,RV_Disc_D12mm_W4.2mm_P7.5mm,TDK/EPCOS S10K150 (B72210S0151K101)
1,RV2,10k RAMP CAL,Potentiometer_Bourns_3296W_Vertical,Bourns 3296W-1-103LF
1,RV3,10k MAX POWER,Potentiometer_Bourns_3296W_Vertical,Bourns 3296W-1-103LF
1,T1,BV301D24028,Zettler_EI30_2xSec,"Zettler Magnetics BV301D24028 (115V, 2x24V 58mA, 2.8VA)"
2,T2 T3,P0584ANL,Pulse_P0584ANL,Pulse P0584ANL
1,TP1,RAMP,TestPoint_Loop_D2.50mm_Drill1.0mm,
1,TP2,FIRE_THRESHOLD,TestPoint_Loop_D2.50mm_Drill1.0mm,
1,TP3,HALF_L_POS,TestPoint_Loop_D2.50mm_Drill1.0mm,
1,TP4,HALF_L_NEG,TestPoint_Loop_D2.50mm_Drill1.0mm,
1,TP5,ZERO_CROSS,TestPoint_Loop_D2.50mm_Drill1.0mm,
1,TP6,FIRE_AND_ENABLE,TestPoint_Loop_D2.50mm_Drill1.0mm,
1,TP7,PULSE_TRAIN,TestPoint_Loop_D2.50mm_Drill1.0mm,
2,TP8 TP10,GND,TestPoint_Loop_D2.50mm_Drill1.0mm,
1,TP9,SYNC_L_SENSE,TestPoint_Loop_D2.50mm_Drill1.0mm,
1,TP11,VGDT,TestPoint_Loop_D2.50mm_Drill1.0mm,
1,U1,LM317HVT,TO-220-3_Vertical,TI LM317HVT (60V) - fit a small clip-on heatsink
1,U2,L7805,TO-220-3_Vertical,ST L7805CV
1,U3,LM339,SOIC-14_3.9x8.7mm_P1.27mm,TI LM339DR
1,U4,MCP6002,SOIC-8_3.9x4.9mm_P1.27mm,Microchip MCP6002-I/SN
1,U5,TLC555,SOIC-8_3.9x4.9mm_P1.27mm,TI TLC555CDR (CMOS 555 - not NE555)
1,U6,74HC08,SOIC-14_3.9x8.7mm_P1.27mm,74HC08D (e.g. Nexperia 74HC08D or TI SN74HC08DR)
1,U7,LM317HVT,TO-220-3_Vertical,TI LM317HVT (60V)
1,U8,74AHC1G02,SOT-23-5,"TI SN74AHC1G02DBVR (single NOR, Schmitt inputs, SOT-23-5); 74LVC1G02 also fits"
